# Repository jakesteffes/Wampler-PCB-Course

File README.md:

# File Repository for the Wampler PCB Course

Welcome! Download the related course files below:

### File Downloads
[How to Design PCBs for DIY Guitar Pedals](https://github.com/jakesteffes/Wampler-PCB-Course/releases/download/PCB_Course_1/HowToDesignPCBsForDIYGuitarPedals.zip)

[KiCad Libraries](https://github.com/jakesteffes/Wampler-PCB-Course/releases/download/KiCadLibraries/KiCad.Libraries.zip)

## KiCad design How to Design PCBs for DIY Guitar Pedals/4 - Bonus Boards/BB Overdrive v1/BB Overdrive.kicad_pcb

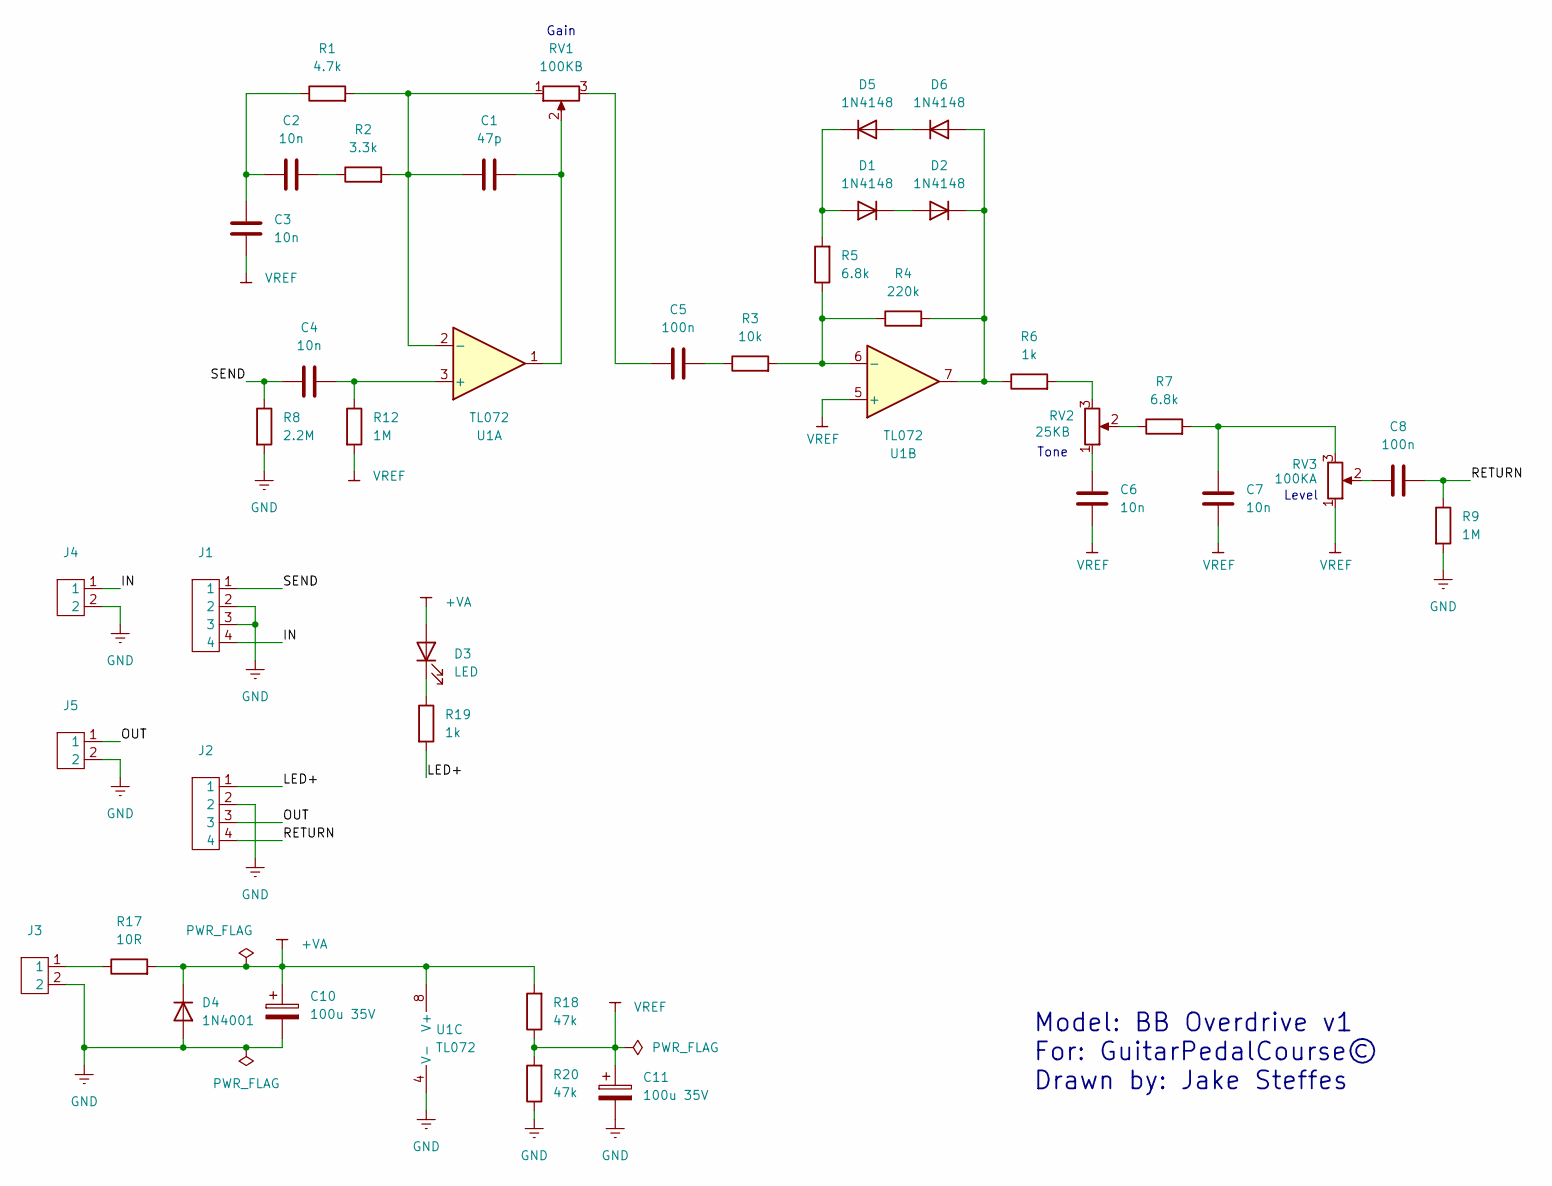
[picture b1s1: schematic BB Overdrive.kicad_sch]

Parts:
C1: 47p; CAP_MLCC_47PF
C2, C3, C4, C6, C7: 10n; CAP_FILM_10NF
C5, C8: 100n; CAP_FILM_100NF
C10, C11: 100u 35V; CAP_ELEC_100UF
D1, D2, D5, D6: 1N4148; DIODE_1N4148
D3: LED; LED_5MM
D4: 1N4001; DIODE_1N4001
J1, J2: CONNECTOR_4
J3, J4, J5: CONNECTOR_2
R1: 4.7k; RESISTOR_1_4W
R2: 3.3k; RESISTOR_1_4W
R3: 10k; RESISTOR_1_4W
R4: 220k; RESISTOR_1_4W
R5, R7: 6.8k; RESISTOR_1_4W
R6, R19: 1k; RESISTOR_1_4W
R8: 2.2M; RESISTOR_1_4W
R9, R12: 1M; RESISTOR_1_4W
R17: 10R; RESISTOR_1_4W
R18, R20: 47k; RESISTOR_1_4W
RV1: 100KB; POT_16MM_RA
RV2: 25KB; POT_16MM_RA
RV3: 100KA; POT_16MM_RA
U1: TL072; OP_AMP

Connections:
+VA: C10.1, D3.2 (A), D4.1 (K), R17.2, R18.2, U1.8 (V+)
/IN: J1.4, J4.1
/LED+: J2.1, R19.2
/OUT: J2.3, J5.1
/RETURN: C8.2, J2.4, R9.1
/SEND: C4.1, J1.1, R8.1
GND: C10.2, C11.2, D4.2 (A), J1.2, J1.3, J2.2, J3.2, J4.2, J5.2, R8.2, R9.2, R20.1, U1.4 (V-)
unnamed: C1.2, RV1.2, U1.1
unnamed: C2.1, C3.2, R1.1
unnamed: C2.2, R2.1
unnamed: C5.1, RV1.3
unnamed: C5.2, R3.1
unnamed: C6.2, RV2.1
unnamed: C7.2, R7.2, RV3.3
unnamed: C8.1, RV3.2
unnamed: D1.2 (A), D5.1 (K), R5.2
unnamed: D1.1 (K), D2.2 (A)
unnamed: D2.1 (K), D6.2 (A), R4.2, R6.1, U1.7
unnamed: D3.1 (K), R19.1
unnamed: D5.2 (A), D6.1 (K)
unnamed: J3.1, R17.1
unnamed: R6.2, RV2.3
unnamed: R7.1, RV2.2
unnamed: C4.2, R12.1, U1.3 (+)
unnamed: C1.1, R1.2, R2.2, RV1.1, U1.2 (-)
unnamed: R3.2, R4.1, R5.1, U1.6 (-)
VREF: C3.1, C6.1, C7.1, C11.1, R12.2, R18.1, R20.2, RV3.1, U1.5 (+)

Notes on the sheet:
Model: BB Overdrive v1 For: GuitarPedalCourse© Drawn by: Jake Steffes
Level
Tone
Gain

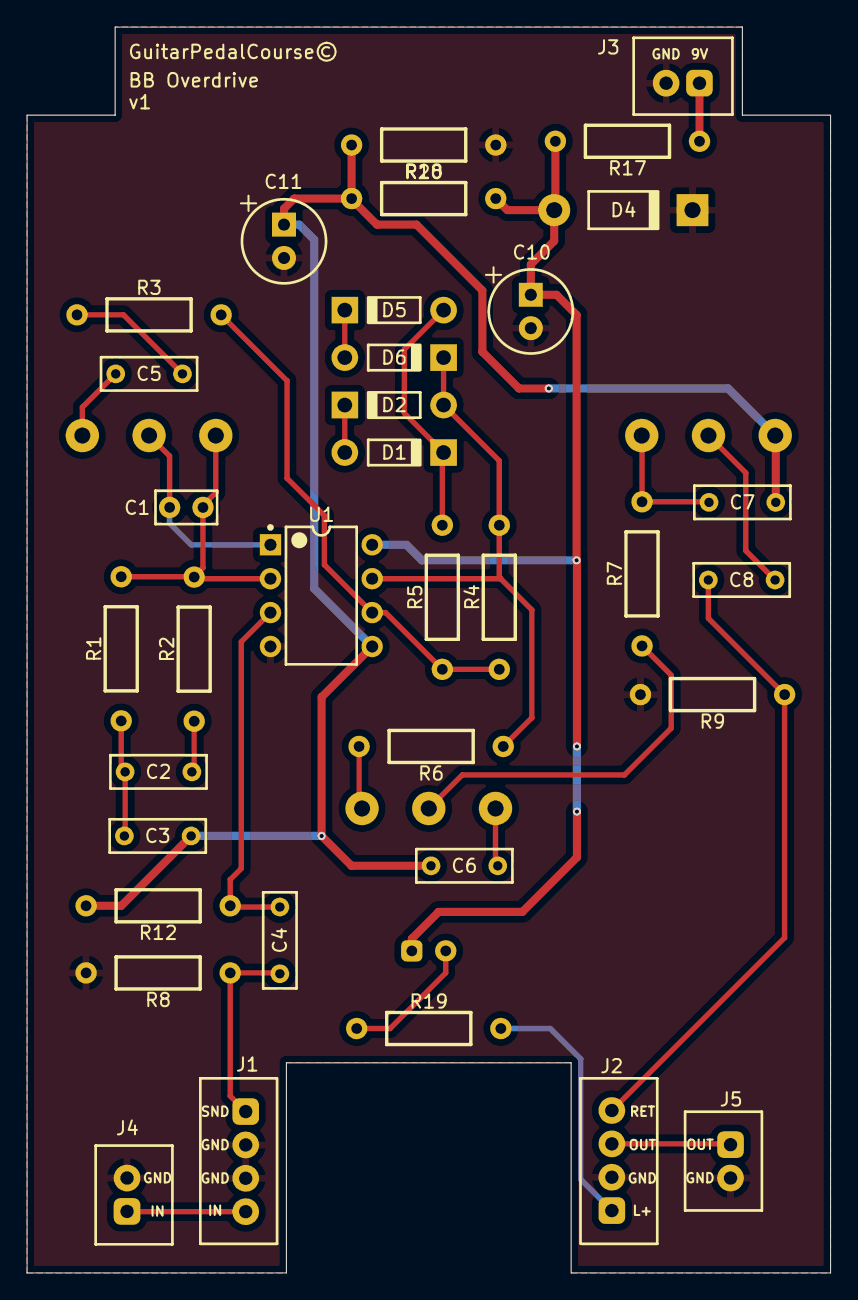
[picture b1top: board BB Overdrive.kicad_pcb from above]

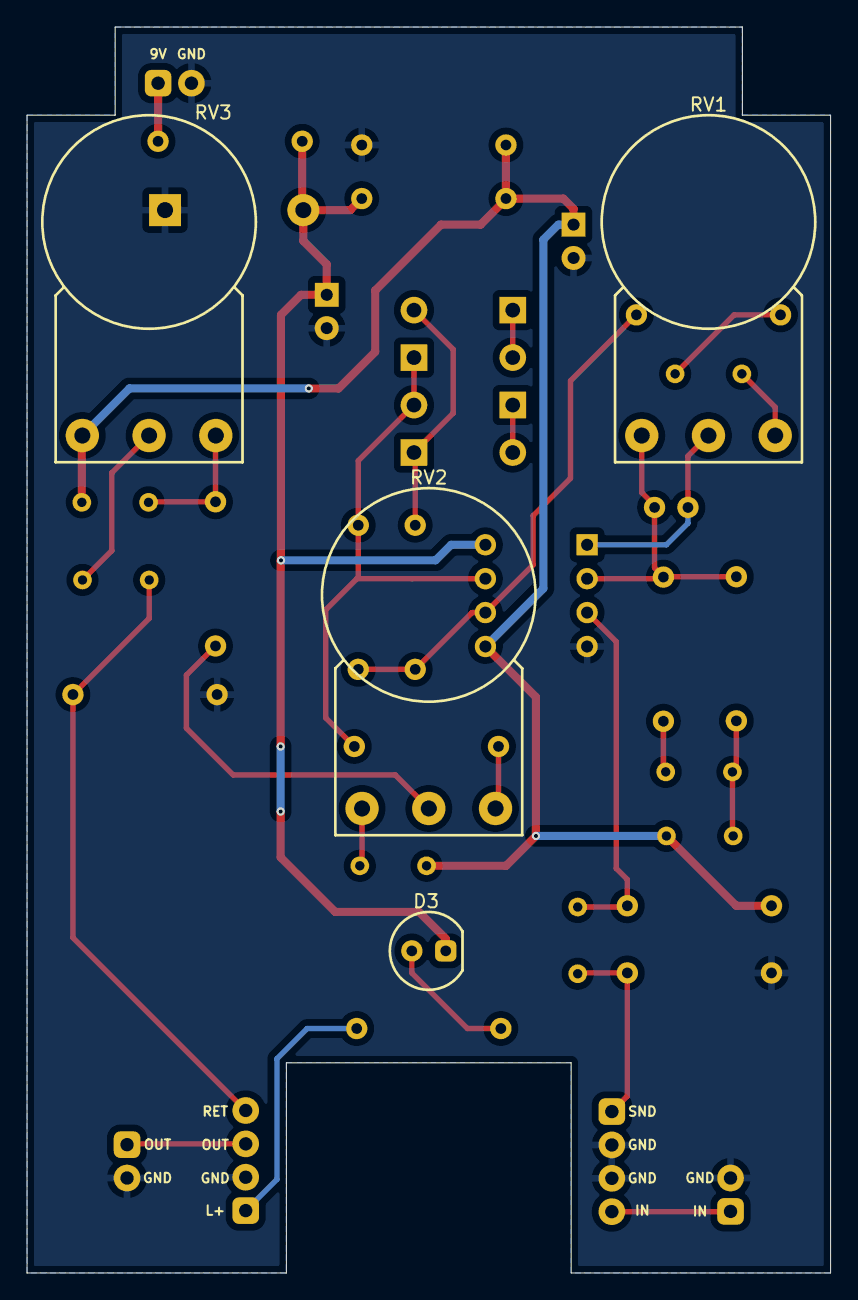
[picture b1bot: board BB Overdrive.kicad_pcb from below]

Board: 2 copper layers, 60.2 x 93.3 mm, 39 parts (4 on the bottom side), 27 nets.

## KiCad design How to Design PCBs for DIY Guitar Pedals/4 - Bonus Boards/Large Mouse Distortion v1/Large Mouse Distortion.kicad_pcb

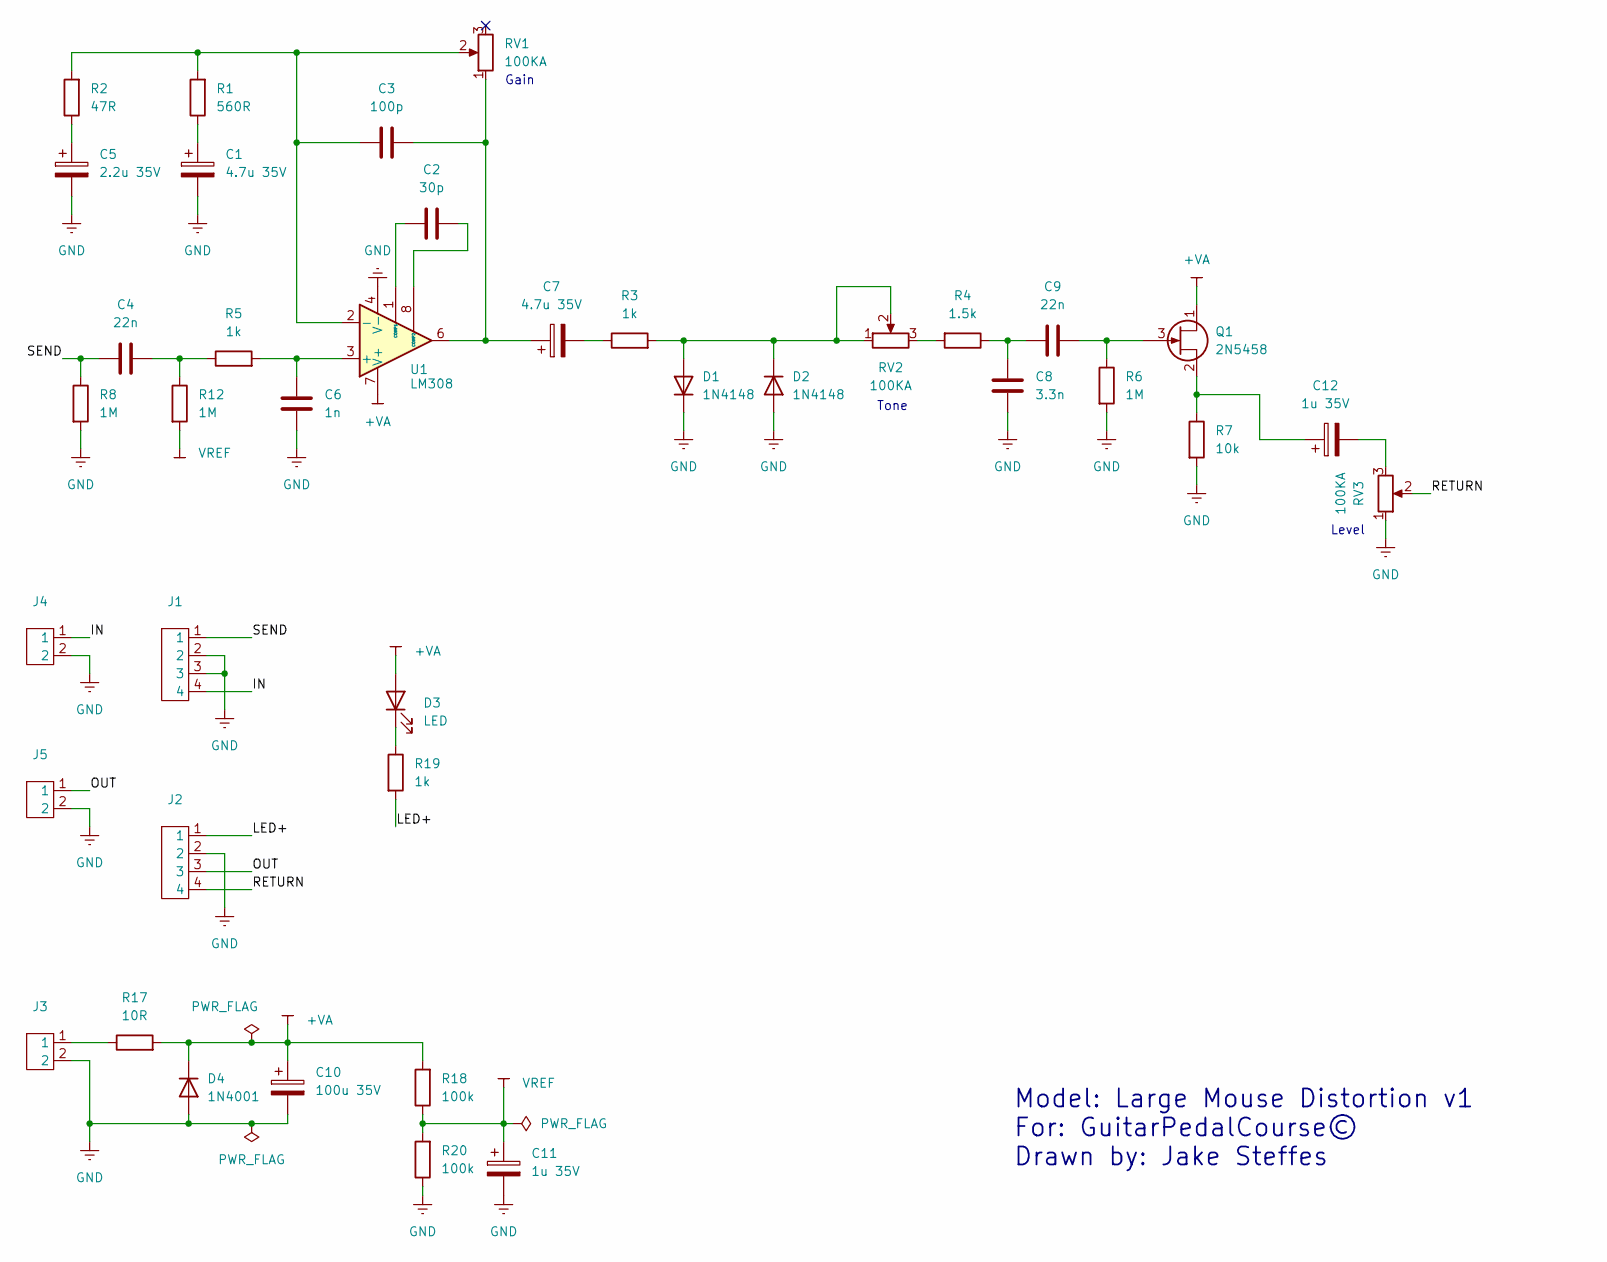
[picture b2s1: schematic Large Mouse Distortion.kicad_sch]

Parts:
C1, C7: 4.7u 35V; CAP_ELEC_4.7UF
C2: 30p; CAP_MLCC_30PF
C3: 100p; CAP_MLCC_100PF
C4, C9: 22n; CAP_FILM_22NF
C5: 2.2u 35V; CAP_ELEC_2.2UF
C6: 1n; CAP_MLCC_1NF
C8: 3.3n; CAP_MLCC_3.3NF
C10: 100u 35V; CAP_ELEC_100UF
C11, C12: 1u 35V; CAP_ELEC_1UF
D1, D2: 1N4148; DIODE_1N4148
D3: LED; LED_5MM
D4: 1N4001; DIODE_1N4001
J1, J2: CONNECTOR_4
J3, J4, J5: CONNECTOR_2
Q1: 2N5458; BJT_2N5458
R1: 560R; RESISTOR_1_4W
R2: 47R; RESISTOR_1_4W
R3, R5, R19: 1k; RESISTOR_1_4W
R4: 1.5k; RESISTOR_1_4W
R6, R8, R12: 1M; RESISTOR_1_4W
R7: 10k; RESISTOR_1_4W
R17: 10R; RESISTOR_1_4W
R18, R20: 100k; RESISTOR_1_4W
RV1, RV2, RV3: 100KA; POT_16MM_RA
U1: LM308; OP_AMP

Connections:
+VA: C10.1, D3.2 (A), D4.1 (K), Q1.1 (D), R17.2, R18.2, U1.7 (V+)
/IN: J1.4, J4.1
/LED+: J2.1, R19.2
/OUT: J2.3, J5.1
/RETURN: J2.4, RV3.2
/SEND: C4.1, J1.1, R8.1
GND: C1.2, C5.2, C6.2, C8.2, C10.2, C11.2, D1.1 (K), D2.2 (A), D4.2 (A), J1.2, J1.3, J2.2, J3.2, J4.2, J5.2, R6.2, R7.2, R8.2, R20.1, RV3.1, U1.4 (V-)
unnamed: C1.1, R1.1
unnamed: C3.2, C7.1, RV1.1, U1.6
unnamed: C4.2, R5.1, R12.1
unnamed: C5.1, R2.1
unnamed: C7.2, R3.1
unnamed: C8.1, C9.1, R4.1
unnamed: C12.2, RV3.3
unnamed: D1.2 (A), D2.1 (K), R3.2, RV2.1, RV2.2
unnamed: D3.1 (K), R19.1
unnamed: J3.1, R17.1
unnamed: C9.2, Q1.3 (G), R6.1
unnamed: C12.1, Q1.2 (S), R7.1
unnamed: R4.2, RV2.3
unnamed: C6.1, R5.2, U1.3 (+)
unnamed: C3.1, R1.2, R2.2, RV1.2, U1.2 (-)
unnamed: C2.1, U1.1 (COMP1)
unnamed: C2.2, U1.8 (COMP2)
VREF: C11.1, R12.2, R18.1, R20.2

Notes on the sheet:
Gain
Level
Tone
Model: Large Mouse Distortion v1 For: GuitarPedalCourse© Drawn by: Jake Steffes

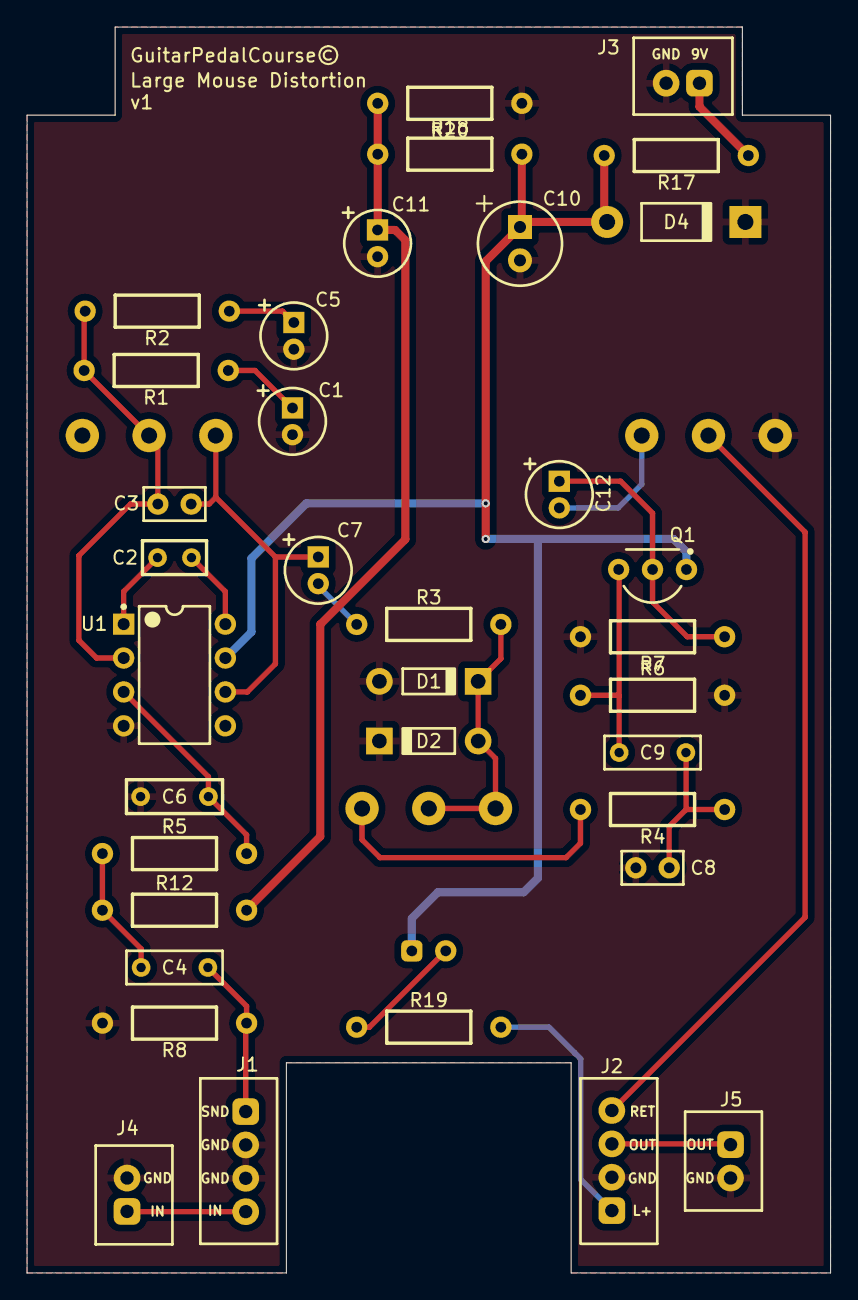
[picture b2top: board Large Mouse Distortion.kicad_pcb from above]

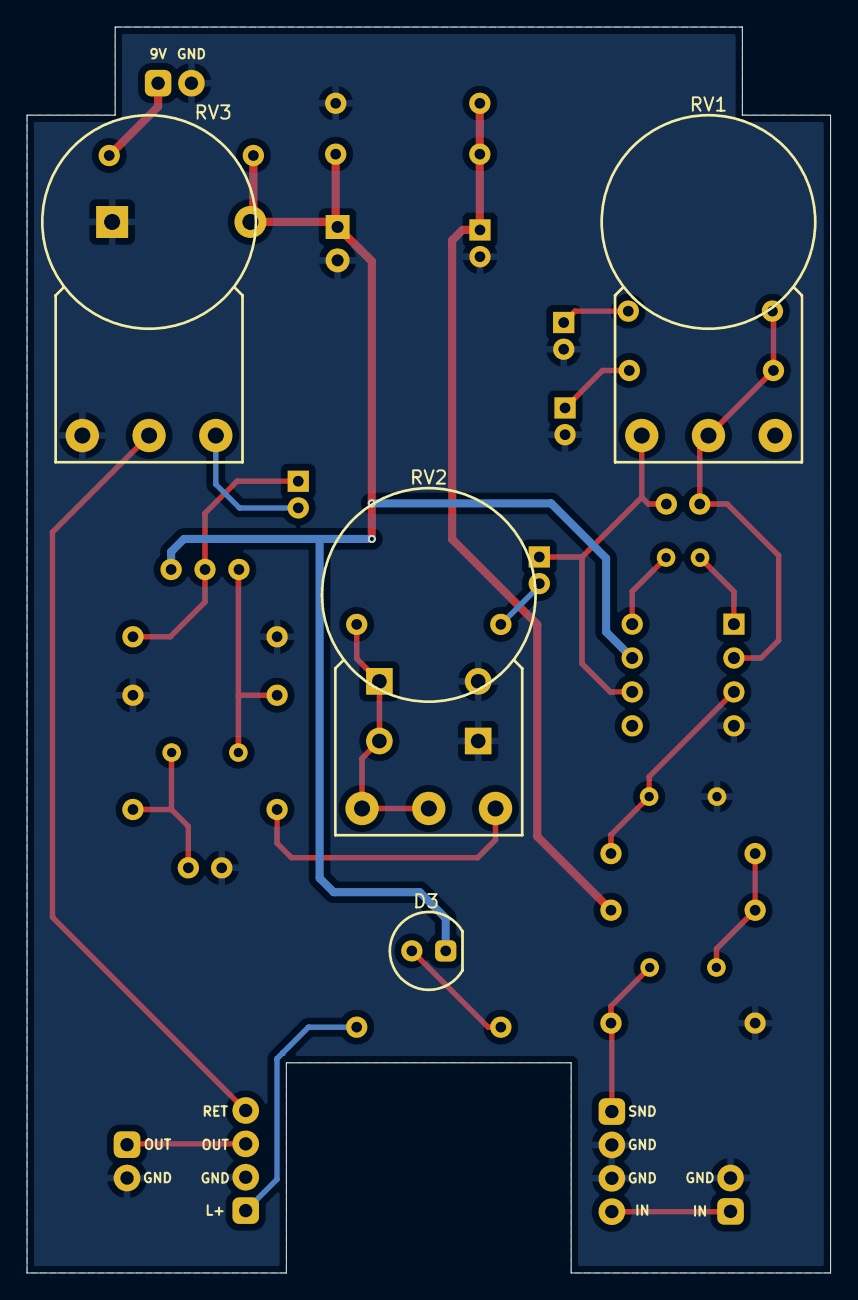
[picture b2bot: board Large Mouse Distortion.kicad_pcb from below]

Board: 2 copper layers, 60.2 x 93.3 mm, 39 parts (4 on the bottom side), 25 nets.

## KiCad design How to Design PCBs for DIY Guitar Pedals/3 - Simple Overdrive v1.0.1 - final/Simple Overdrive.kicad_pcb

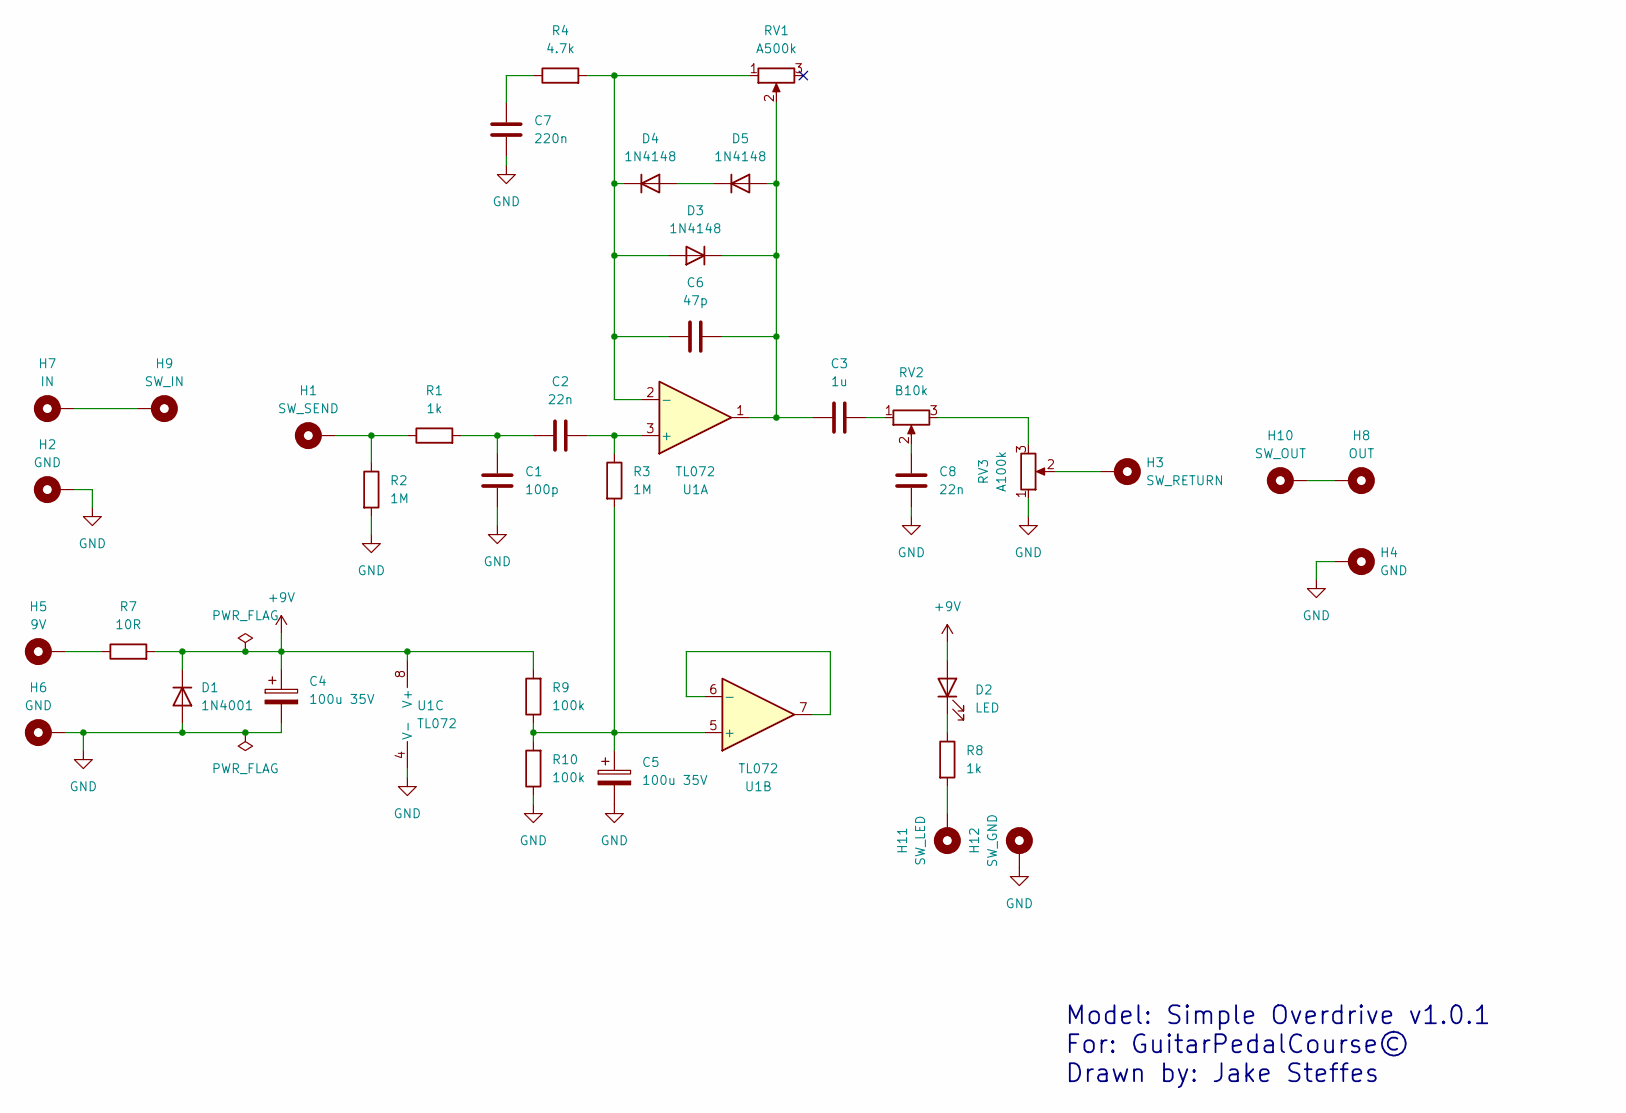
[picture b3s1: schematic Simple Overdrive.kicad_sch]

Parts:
C1: 100p; C_Rect_L7.0mm_W4.5mm_P5.00mm
C2, C8: 22n; C_Rect_L7.2mm_W2.5mm_P5.00mm_FKS2_FKP2_MKS2_MKP2
C3: 1u; C_Rect_L7.2mm_W5.5mm_P5.00mm_FKS2_FKP2_MKS2_MKP2
C4, C5: 100u 35V; CP_Radial_D6.3mm_P2.50mm
C6: 47p; C_Rect_L7.0mm_W2.5mm_P5.00mm
C7: 220n; C_Rect_L7.2mm_W2.5mm_P5.00mm_FKS2_FKP2_MKS2_MKP2
D1: 1N4001; D_DO-41_SOD81_P10.16mm_Horizontal
D2: LED; LED_D5.0mm
D3, D4, D5: 1N4148; D_DO-35_SOD27_P7.62mm_Horizontal
H1: SW_SEND; PAD_4MM
H2, H4, H6: GND; PAD_4MM
H3: SW_RETURN; PAD_4MM
H5: 9V; PAD_4MM
H7: IN; PAD_4MM
H8: OUT; PAD_4MM
H9: SW_IN; PAD_4MM
H10: SW_OUT; PAD_4MM
H11: SW_LED; PAD_4MM
H12: SW_GND; PAD_4MM
R1, R8: 1k; R_Axial_DIN0207_L6.3mm_D2.5mm_P7.62mm_Horizontal
R2, R3: 1M; R_Axial_DIN0207_L6.3mm_D2.5mm_P7.62mm_Horizontal
R4: 4.7k; R_Axial_DIN0207_L6.3mm_D2.5mm_P7.62mm_Horizontal
R7: 10R; R_Axial_DIN0207_L6.3mm_D2.5mm_P7.62mm_Horizontal
R9, R10: 100k; R_Axial_DIN0207_L6.3mm_D2.5mm_P7.62mm_Horizontal
RV1: A500k; POT_9MM_RA
RV2: B10k; POT_9MM_RA
RV3: A100k; POT_9MM_RA
U1: TL072; DIP-8_W7.62mm

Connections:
+9V: C4.1, D1.1 (K), D2.2 (A), R7.2, R9.2, U1.8 (V+)
GND: C1.2, C4.2, C5.2, C7.1, C8.1, D1.2 (A), H2.1, H4.1, H6.1, H12.1, R2.2, R10.1, RV3.1, U1.4 (V-)
unnamed: C1.1, C2.1, R1.2
unnamed: C3.2, RV2.1
unnamed: C7.2, R4.1
unnamed: C8.2, RV2.2
unnamed: D2.1 (K), R8.1
unnamed: C6.1, D3.2 (A), D4.1 (K), R4.2, RV1.1, U1.2 (-)
unnamed: C3.1, C6.2, D3.1 (K), D5.2 (A), RV1.2, U1.1
unnamed: D4.2 (A), D5.1 (K)
unnamed: H1.1, R1.1, R2.1
unnamed: H3.1, RV3.2
unnamed: H5.1, R7.1
unnamed: H7.1, H9.1
unnamed: H8.1, H10.1
unnamed: H11.1, R8.2
unnamed: RV2.3, RV3.3
unnamed: C2.2, R3.1, U1.3 (+)
unnamed: C5.1, R3.2, R9.1, R10.2, U1.5 (+)
unnamed: U1.6 (-), U1.7

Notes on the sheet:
Model: Simple Overdrive v1.0.1 For: GuitarPedalCourse© Drawn by: Jake Steffes

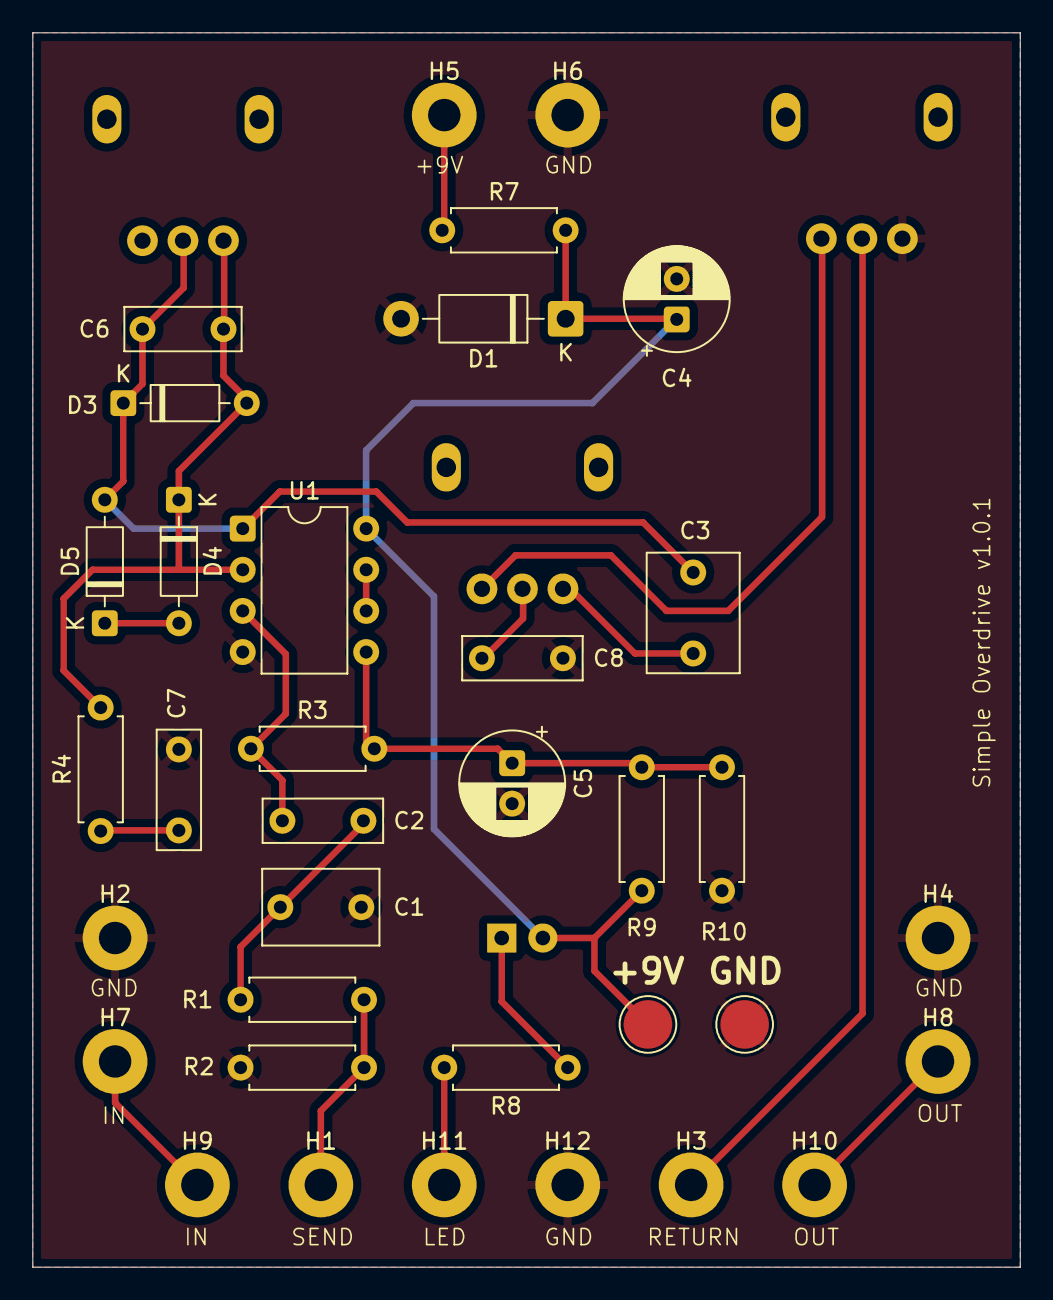
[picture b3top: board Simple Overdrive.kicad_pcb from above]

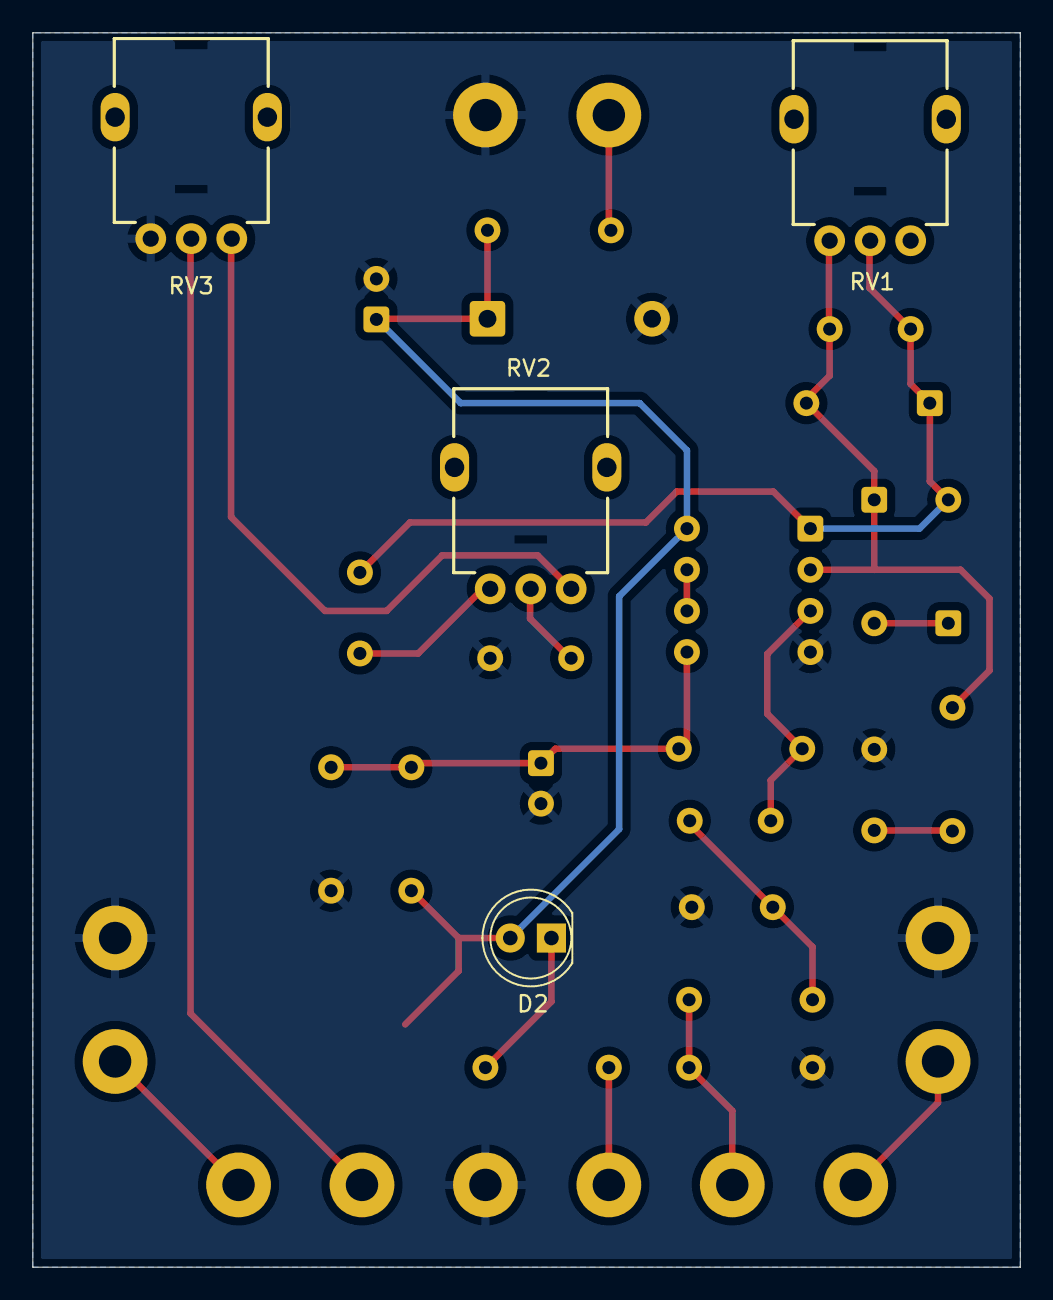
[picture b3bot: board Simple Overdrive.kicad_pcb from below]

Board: 2 copper layers, 61.0 x 76.2 mm, 37 parts (4 on the bottom side), 20 nets.

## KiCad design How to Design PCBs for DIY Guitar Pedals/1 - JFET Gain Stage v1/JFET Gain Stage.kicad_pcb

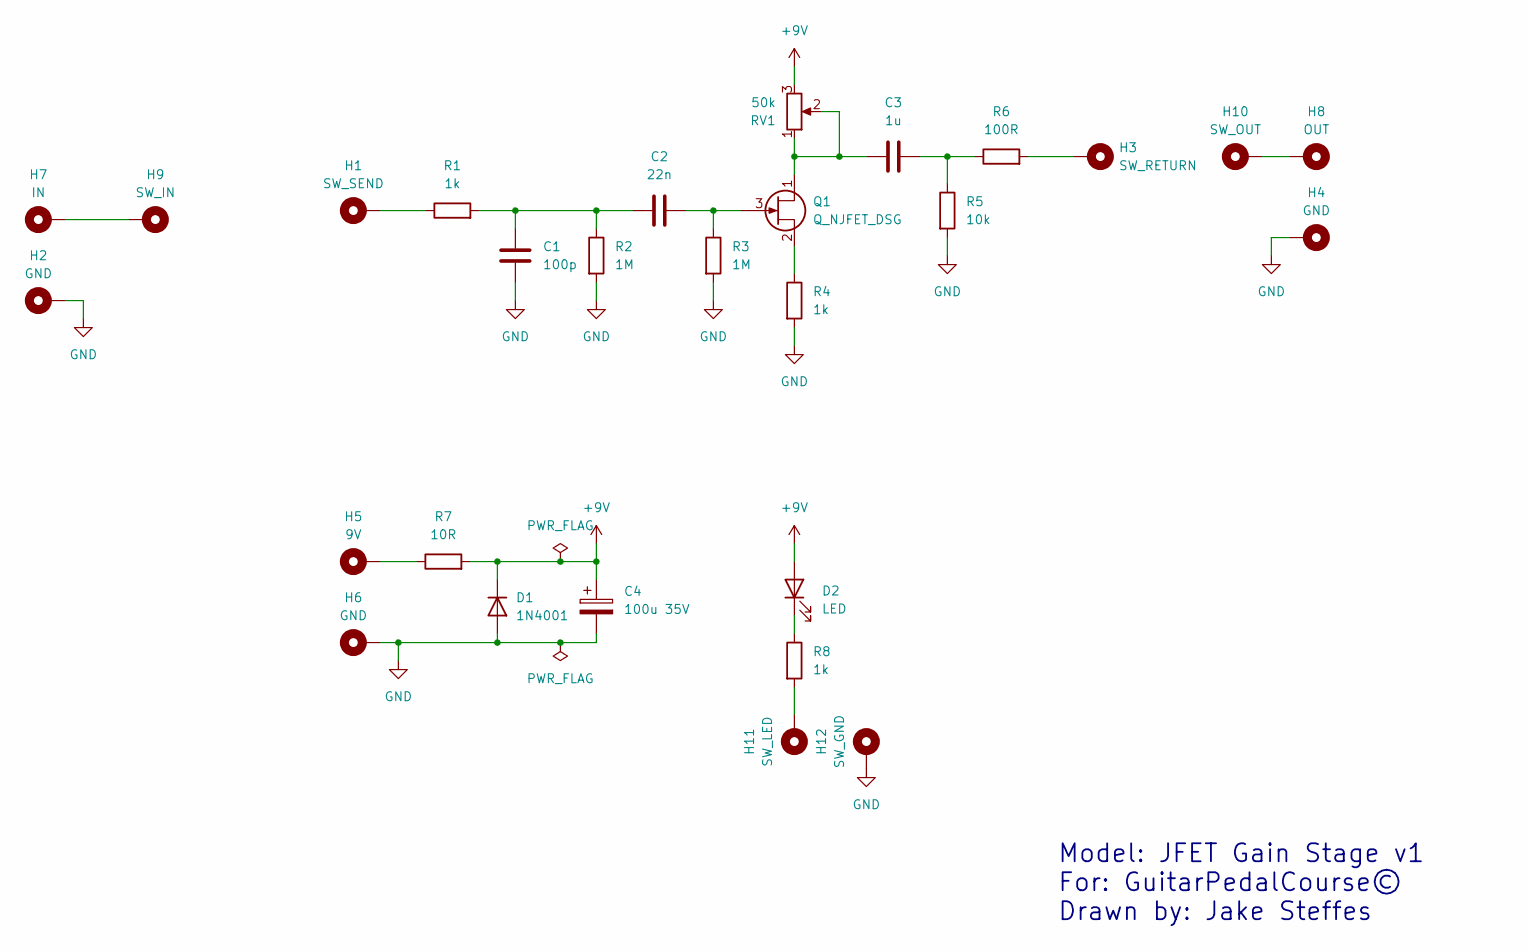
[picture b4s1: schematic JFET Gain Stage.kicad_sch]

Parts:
C1: 100p; C_Rect_L7.0mm_W4.5mm_P5.00mm
C2: 22n; C_Rect_L7.2mm_W2.5mm_P5.00mm_FKS2_FKP2_MKS2_MKP2
C3: 1u; C_Rect_L7.2mm_W5.5mm_P5.00mm_FKS2_FKP2_MKS2_MKP2
C4: 100u 35V; CP_Radial_D6.3mm_P2.50mm
D1: 1N4001; D_DO-41_SOD81_P10.16mm_Horizontal
D2: LED; LED_D5.0mm
H1: SW_SEND; MountingHole_2.2mm_M2_DIN965_Pad_TopBottom
H2, H4, H6: GND; MountingHole_2.2mm_M2_DIN965_Pad_TopBottom
H3: SW_RETURN; MountingHole_2.2mm_M2_DIN965_Pad_TopBottom
H5: 9V; MountingHole_2.2mm_M2_DIN965_Pad_TopBottom
H7: IN; MountingHole_2.2mm_M2_DIN965_Pad_TopBottom
H8: OUT; MountingHole_2.2mm_M2_DIN965_Pad_TopBottom
H9: SW_IN; MountingHole_2.2mm_M2_DIN965_Pad_TopBottom
H10: SW_OUT; MountingHole_2.2mm_M2_DIN965_Pad_TopBottom
H11: SW_LED; MountingHole_2.2mm_M2_DIN965_Pad_TopBottom
H12: SW_GND; MountingHole_2.2mm_M2_DIN965_Pad_TopBottom
Q1: Q_NJFET_DSG; TO-92
R1, R4, R8: 1k; R_Axial_DIN0207_L6.3mm_D2.5mm_P7.62mm_Horizontal
R2, R3: 1M; R_Axial_DIN0207_L6.3mm_D2.5mm_P7.62mm_Horizontal
R5: 10k; R_Axial_DIN0207_L6.3mm_D2.5mm_P7.62mm_Horizontal
R6: 100R; R_Axial_DIN0207_L6.3mm_D2.5mm_P7.62mm_Horizontal
R7: 10R; R_Axial_DIN0207_L6.3mm_D2.5mm_P7.62mm_Horizontal
RV1: 50k; Potentiometer_Bourns_3386F_Vertical

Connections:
+9V: C4.1, D1.1 (K), D2.2 (A), R7.2, RV1.3; also elsewhere on the board
GND: C1.2, C4.2, D1.2 (A), H2.1, H4.1, H6.1, H12.1, R2.2, R3.2, R4.2, R5.2; also elsewhere on the board
unnamed: C1.1, C2.1, R1.2, R2.1
unnamed: C3.2, R5.1, R6.1
unnamed: D2.1 (K), R8.1
unnamed: H1.1, R1.1
unnamed: H3.1, R6.2
unnamed: H5.1, R7.1
unnamed: H7.1, H9.1
unnamed: H8.1, H10.1
unnamed: H11.1, R8.2
unnamed 11: C3.1, Q1.1 (D), RV1.1, RV1.2; also elsewhere on the board
unnamed: C2.2, Q1.3 (G), R3.1
unnamed: Q1.2 (S), R4.1

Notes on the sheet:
Model: JFET Gain Stage v1 For: GuitarPedalCourse© Drawn by: Jake Steffes

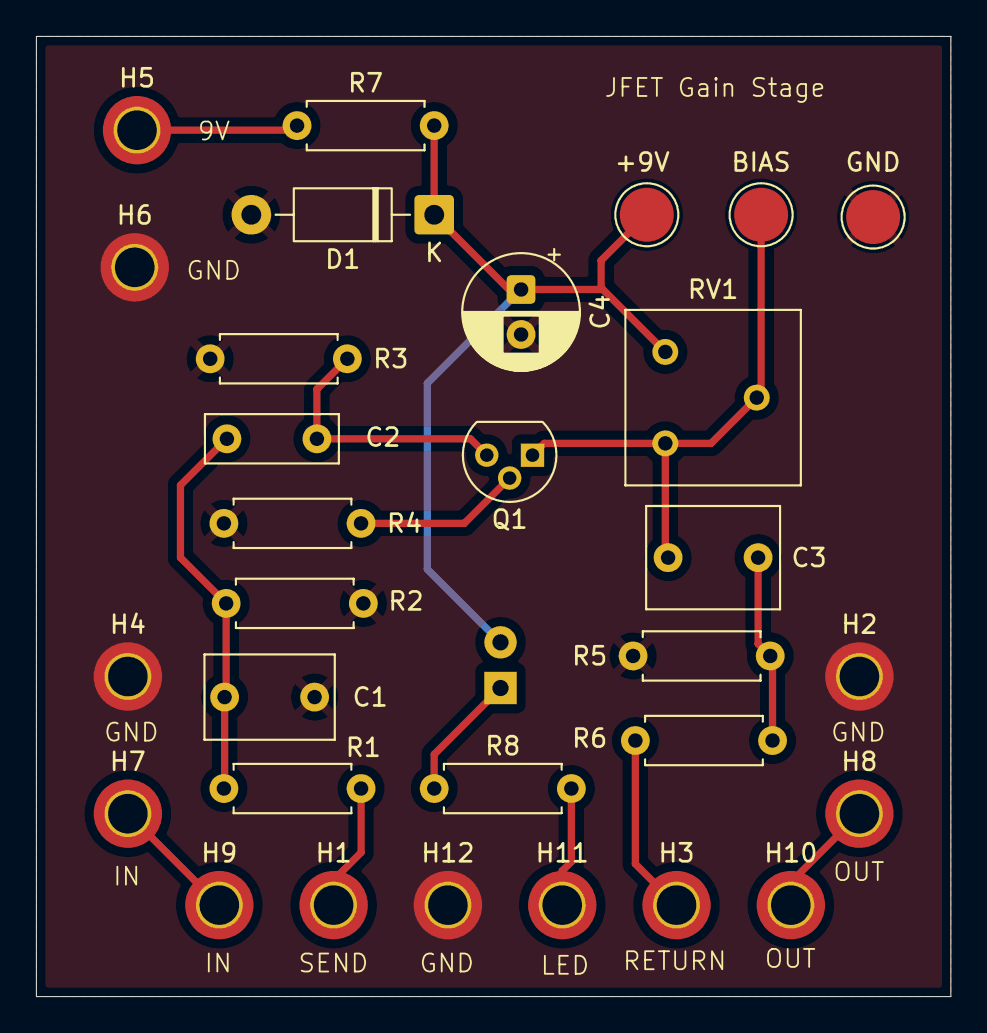
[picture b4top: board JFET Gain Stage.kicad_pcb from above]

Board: 2 copper layers, 50.8 x 53.3 mm, 31 parts (1 on the bottom side), 14 nets.

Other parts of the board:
+9V: TestPoint_Pad_D3.0mm
BIAS: TestPoint_Pad_D3.0mm
GND: TestPoint_Pad_D3.0mm

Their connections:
+9V: +9V.1; also elsewhere on the board
GND: GND.1; also elsewhere on the board
unnamed 11: BIAS.1; also elsewhere on the board

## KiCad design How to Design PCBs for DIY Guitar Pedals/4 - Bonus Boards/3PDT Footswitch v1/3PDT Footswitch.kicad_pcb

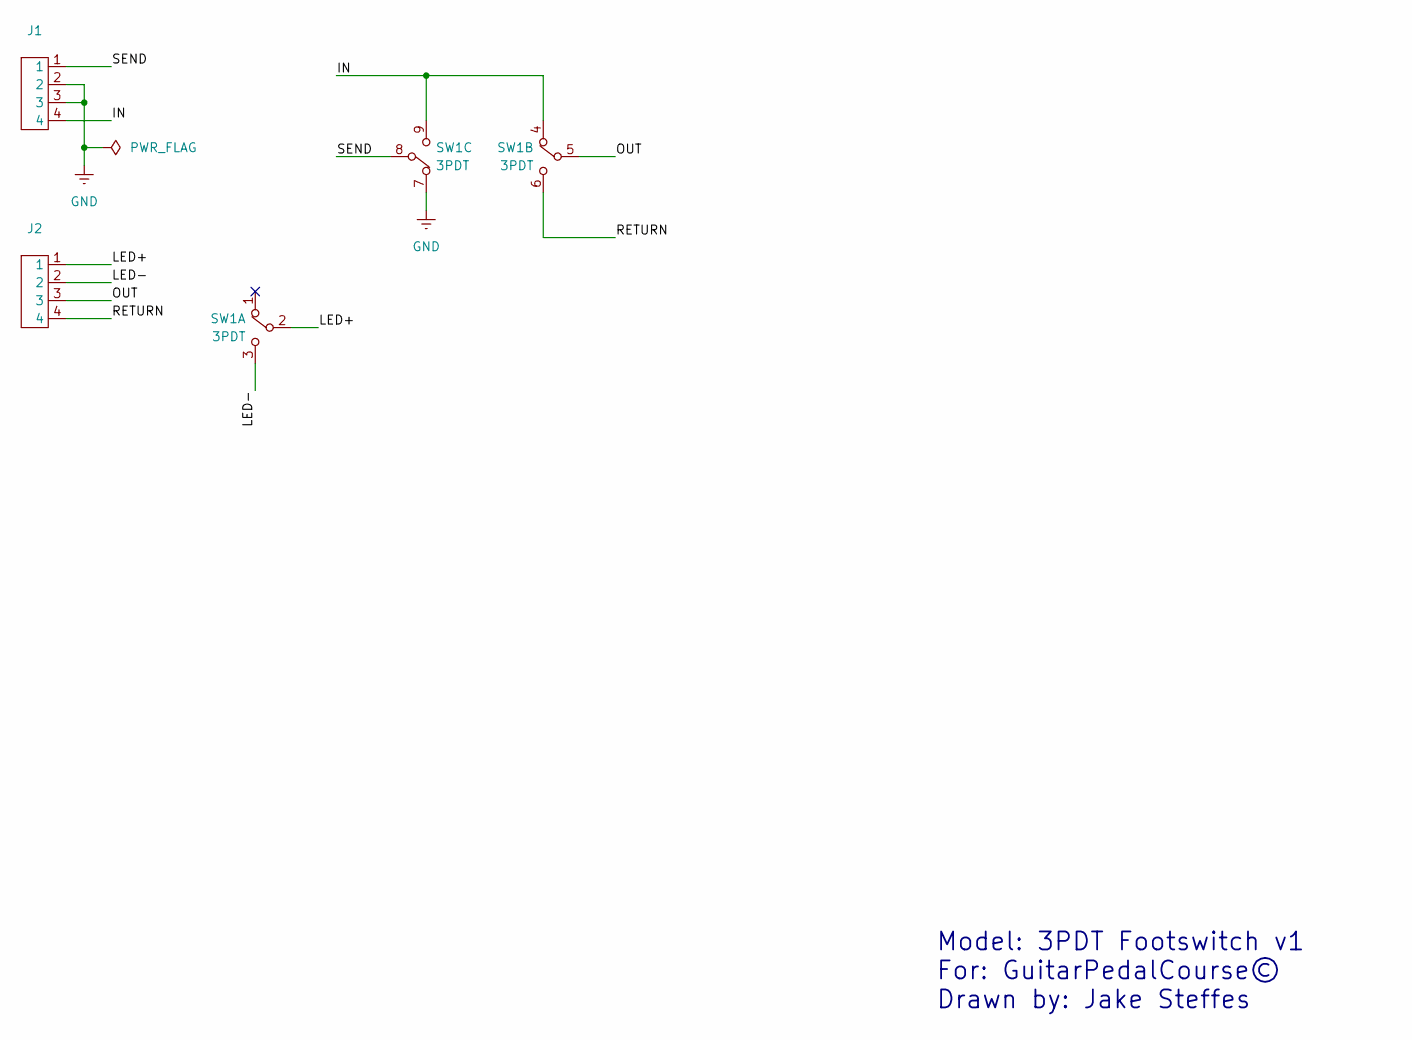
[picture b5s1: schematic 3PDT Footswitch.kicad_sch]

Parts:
J1, J2: CONNECTOR_4
SW1: 3PDT; SW_FOOT_3PDT

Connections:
/IN: J1.4, SW1.4, SW1.9
/LED+: J2.1, SW1.2
/LED-: J2.2, SW1.3
/OUT: J2.3, SW1.5
/RETURN: J2.4, SW1.6
/SEND: J1.1, SW1.8
GND: J1.2, J1.3, SW1.7

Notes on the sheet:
Model: 3PDT Footswitch v1 For: GuitarPedalCourse© Drawn by: Jake Steffes

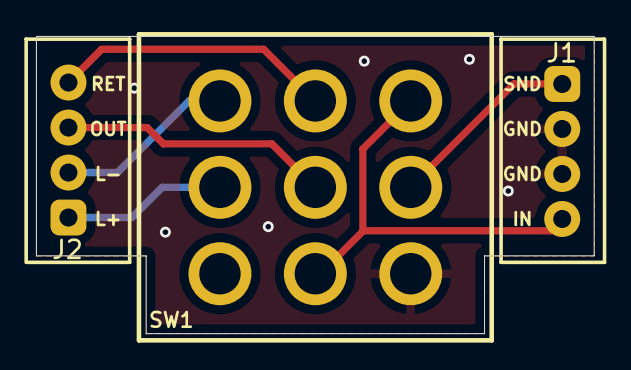
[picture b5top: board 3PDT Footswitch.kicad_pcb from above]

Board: 2 copper layers, 31.0 x 16.5 mm, 3 parts (0 on the bottom side), 7 nets.
